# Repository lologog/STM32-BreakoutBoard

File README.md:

# STM32 Breakout Board

A minimalist development board for STM32, allowing easy connection to the microcontroller and testing its capabilities.

## Project Description
This board is designed for prototyping with STM32 microcontrollers. It enables easy access to processor pins and testing its functions without requiring ready-made kits such as Nucleo or Discovery. The project includes:

- **Microcontroller:** STM32L476RGT6
- **Power Supply:** 5V (barrel connector)
- **Programming:** STLINK-V3MINIE
- **LED Indicators:** Red LED indicating power supply
- **Easy access to GPIO pins**

---

## PCB Rendering
Below is a 3D render generated in KiCad:

<div align="center">
    
</div>

---

## Real-World Implementation
This is the completed PCB:

<div align="center">
    
</div>

---

## Presentation
Below is an animated preview of the board in action:

<div align="center">
    
</div>

---

## Usage Instructions
1. Connect a 5V power supply to the barrel connector.
2. Connect the **STLINK-V3MINIE** programmer.
3. Upload test firmware.
4. Test GPIO pin functionality and develop your applications.

## Author
- **Name**: Krzysztof Tomicki
- **Contact**: tomicki.krzysztof.pv@gmail.com

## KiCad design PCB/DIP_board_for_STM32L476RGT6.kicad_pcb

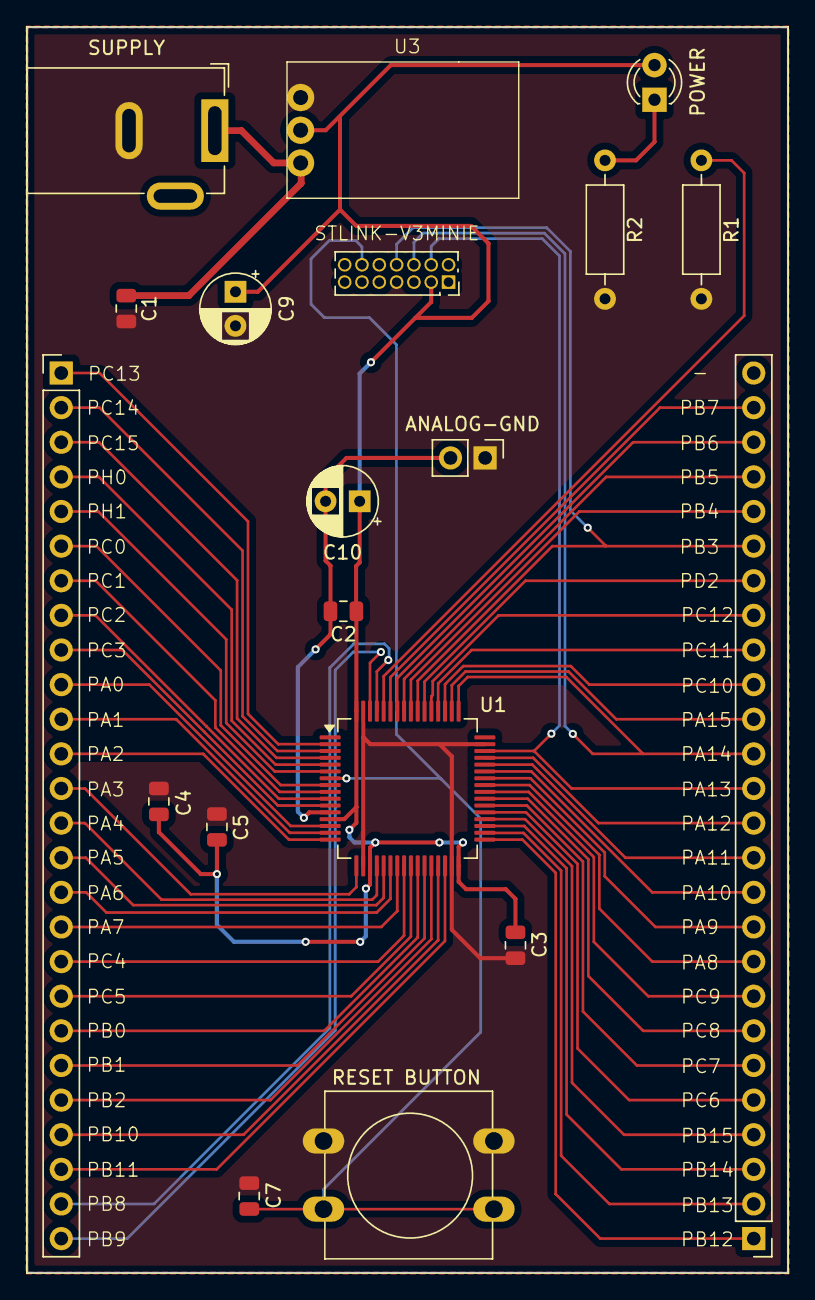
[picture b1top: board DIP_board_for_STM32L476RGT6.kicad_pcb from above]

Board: 2 copper layers, 55.7 x 91.3 mm, 19 parts (0 on the bottom side), 58 nets.

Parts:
ANALOG-GND: Jumper_2_Bridged; PinHeader_1x02_P2.54mm_Vertical
C1, C2, C3, C4, C5, C7: 100n; C_0805_2012Metric
C9, C10: 10u; CP_Radial_D5.0mm_P2.50mm
IDP-14pin-1.27-port1: PinSocket_2x07_P1.27mm_Vertical
J1, J2: Conn_01x26_Pin; PinHeader_1x26_P2.54mm_Vertical
POWER: SUPP_LED; LED_D3.0mm
R1: 100k; R_Axial_DIN0207_L6.3mm_D2.5mm_P10.16mm_Horizontal
R2: 330; R_Axial_DIN0207_L6.3mm_D2.5mm_P10.16mm_Horizontal
RESET BUTTON: SW_Push; SW_PUSH-12mm
SUPPLY: Barrel_Jack_Switch_Pin3Ring; BarrelJack_GCT_DCJ200-10-A_Horizontal
U1: STM32L476RGTx; LQFP-64_10x10mm_P0.5mm
U3: LD1117S33TR_SOT223; LD1117V33 - tht

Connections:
3V3: C2.1, C3.1, C4.1, C5.1, C9.1, C10.1, IDP-14pin-1.27-port1.3 (VCC), POWER.2 (A), U1.13 (VDDA), U1.19 (VDD), U1.32 (VDD), U1.64 (VDD), U3.2 (VO)
+5V: C1.1, SUPPLY.1, U3.3 (VI)
GND: ANALOG-GND.1 (A), C1.2, C3.2, C4.2, C5.2, C7.2, C9.2, IDP-14pin-1.27-port1.7 (GND), R1.2, R2.2, RESET BUTTON.1, SUPPLY.3, U1.18 (VSS), U1.31 (VSS), U1.47 (VSS), U1.63 (VSS), U3.1 (GND)
GND1: ANALOG-GND.2 (B), C2.2, C10.2, U1.12 (VSSA)
NRST: C7.1, IDP-14pin-1.27-port1.12 (RESET), RESET BUTTON.2, U1.7 (NRST)
unnamed: POWER.1 (K), R2.1
unnamed: R1.1, U1.60 (BOOT0)
PA0: J1.10, U1.14 (PA0)
PA1: J1.11, U1.15 (PA1)
PA2: J1.12, U1.16 (PA2)
PA3: J1.13, U1.17 (PA3)
PA4: J1.14, U1.20 (PA4)
PA5: J1.15, U1.21 (PA5)
PA6: J1.16, U1.22 (PA6)
PA7: J1.17, U1.23 (PA7)
PA8: J2.9, U1.41 (PA8)
PA9: J2.10, U1.42 (PA9)
PA10: J2.11, U1.43 (PA10)
PA11: J2.12, U1.44 (PA11)
PA12: J2.13, U1.45 (PA12)
PA13: IDP-14pin-1.27-port1.4 (SWDIO), J2.14, U1.46 (PA13)
PA14: IDP-14pin-1.27-port1.6 (SWCLK), J2.15, U1.49 (PA14)
PA15: J2.16, U1.50 (PA15)
PB0: J1.20, U1.26 (PB0)
PB1: J1.21, U1.27 (PB1)
PB2: J1.22, U1.28 (PB2)
PB3: IDP-14pin-1.27-port1.8 (SWO), J2.21, U1.55 (PB3)
PB4: J2.22, U1.56 (PB4)
PB5: J2.23, U1.57 (PB5)
PB6: J2.24, U1.58 (PB6)
PB7: J2.25, U1.59 (PB7)
PB8: J1.25, U1.61 (PB8)
PB9: J1.26, U1.62 (PB9)
PB10: J1.23, U1.29 (PB10)
PB11: J1.24, U1.30 (PB11)
PB12: J2.1, U1.33 (PB12)
PB13: J2.2, U1.34 (PB13)
PB14: J2.3, U1.35 (PB14)
PB15: J2.4, U1.36 (PB15)
PC0: J1.6, U1.8 (PC0)
PC1: J1.7, U1.9 (PC1)
PC2: J1.8, U1.10 (PC2)
PC3: J1.9, U1.11 (PC3)
PC4: J1.18, U1.24 (PC4)
PC5: J1.19, U1.25 (PC5)
PC6: J2.5, U1.37 (PC6)
PC7: J2.6, U1.38 (PC7)
PC8: J2.7, U1.39 (PC8)
PC9: J2.8, U1.40 (PC9)
PC10: J2.17, U1.51 (PC10)
PC11: J2.18, U1.52 (PC11)
PC12: J2.19, U1.53 (PC12)
PC13: J1.1, U1.2 (PC13)
PC14: J1.2, U1.3 (PC14)
PC15: J1.3, U1.4 (PC15)
PD2: J2.20, U1.54 (PD2)
PH0: J1.4, U1.5 (PH0)
PH1: J1.5, U1.6 (PH1)

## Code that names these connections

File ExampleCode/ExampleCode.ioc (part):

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Mcu.Name=STM32L476R(C-E-G)Tx
Mcu.Package=LQFP64
Mcu.UserName=STM32L476RGTx
PA13\ (JTMS-SWDIO).Mode=Serial_Wire
PA13\ (JTMS-SWDIO).Signal=SYS_JTMS-SWDIO
PA14\ (JTCK-SWCLK).Mode=Serial_Wire
PA14\ (JTCK-SWCLK).Signal=SYS_JTCK-SWCLK
PB12.GPIOParameters=GPIO_PuPd,GPIO_Label
PB12.GPIO_Label=LD1
PB12.GPIO_PuPd=GPIO_PULLDOWN
PB12.Signal=GPIO_Output
PB13.GPIOParameters=GPIO_PuPd,GPIO_Label
PB13.GPIO_Label=LD2
PB13.GPIO_PuPd=GPIO_PULLDOWN
PB13.Signal=GPIO_Output
PB14.GPIOParameters=GPIO_PuPd,GPIO_Label
PB14.GPIO_Label=LD3
PB14.GPIO_PuPd=GPIO_PULLDOWN
PB14.Signal=GPIO_Output
PB15.GPIOParameters=GPIO_PuPd,GPIO_Label
PB15.GPIO_Label=LD4
PB15.GPIO_PuPd=GPIO_PULLDOWN
PB15.Signal=GPIO_Output
PC6.GPIOParameters=GPIO_PuPd,GPIO_Label
PC6.GPIO_Label=LD5
PC6.GPIO_PuPd=GPIO_PULLDOWN
PC6.Signal=GPIO_Output
PC7.GPIOParameters=GPIO_PuPd,GPIO_Label
PC7.GPIO_Label=LD6
PC7.GPIO_PuPd=GPIO_PULLDOWN
PC7.Signal=GPIO_Output
PC8.GPIOParameters=GPIO_PuPd,GPIO_Label
PC8.GPIO_Label=LD7
PC8.GPIO_PuPd=GPIO_PULLDOWN
PC8.Signal=GPIO_Output
RCC.HSE_VALUE=8000000
board=custom

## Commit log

2025-02-06 project: add ExampleCode project files
2025-02-06 project: add ExampleCode logic code with pins added in .ioc
2025-02-06 project: add multimedia for readme file
2025-02-06 Update README.md - add text
2025-02-06 change realisation photo from HEIC to JPG
2025-02-06 Update README.md - change realisation photo from HEIC to JPG
2025-02-06 Update README.md - change realisation photo size
2025-02-06 Update README.md - remove licence
2025-02-06 Update README.md - centering the photos
2025-02-07 Update README.md - correcting small mistake with STLINK-V3MINIE name
2025-03-08 Project: Add new 3D render photo
2025-03-08 Project: Add PCB files
2025-11-02 Add MIT License to the project
